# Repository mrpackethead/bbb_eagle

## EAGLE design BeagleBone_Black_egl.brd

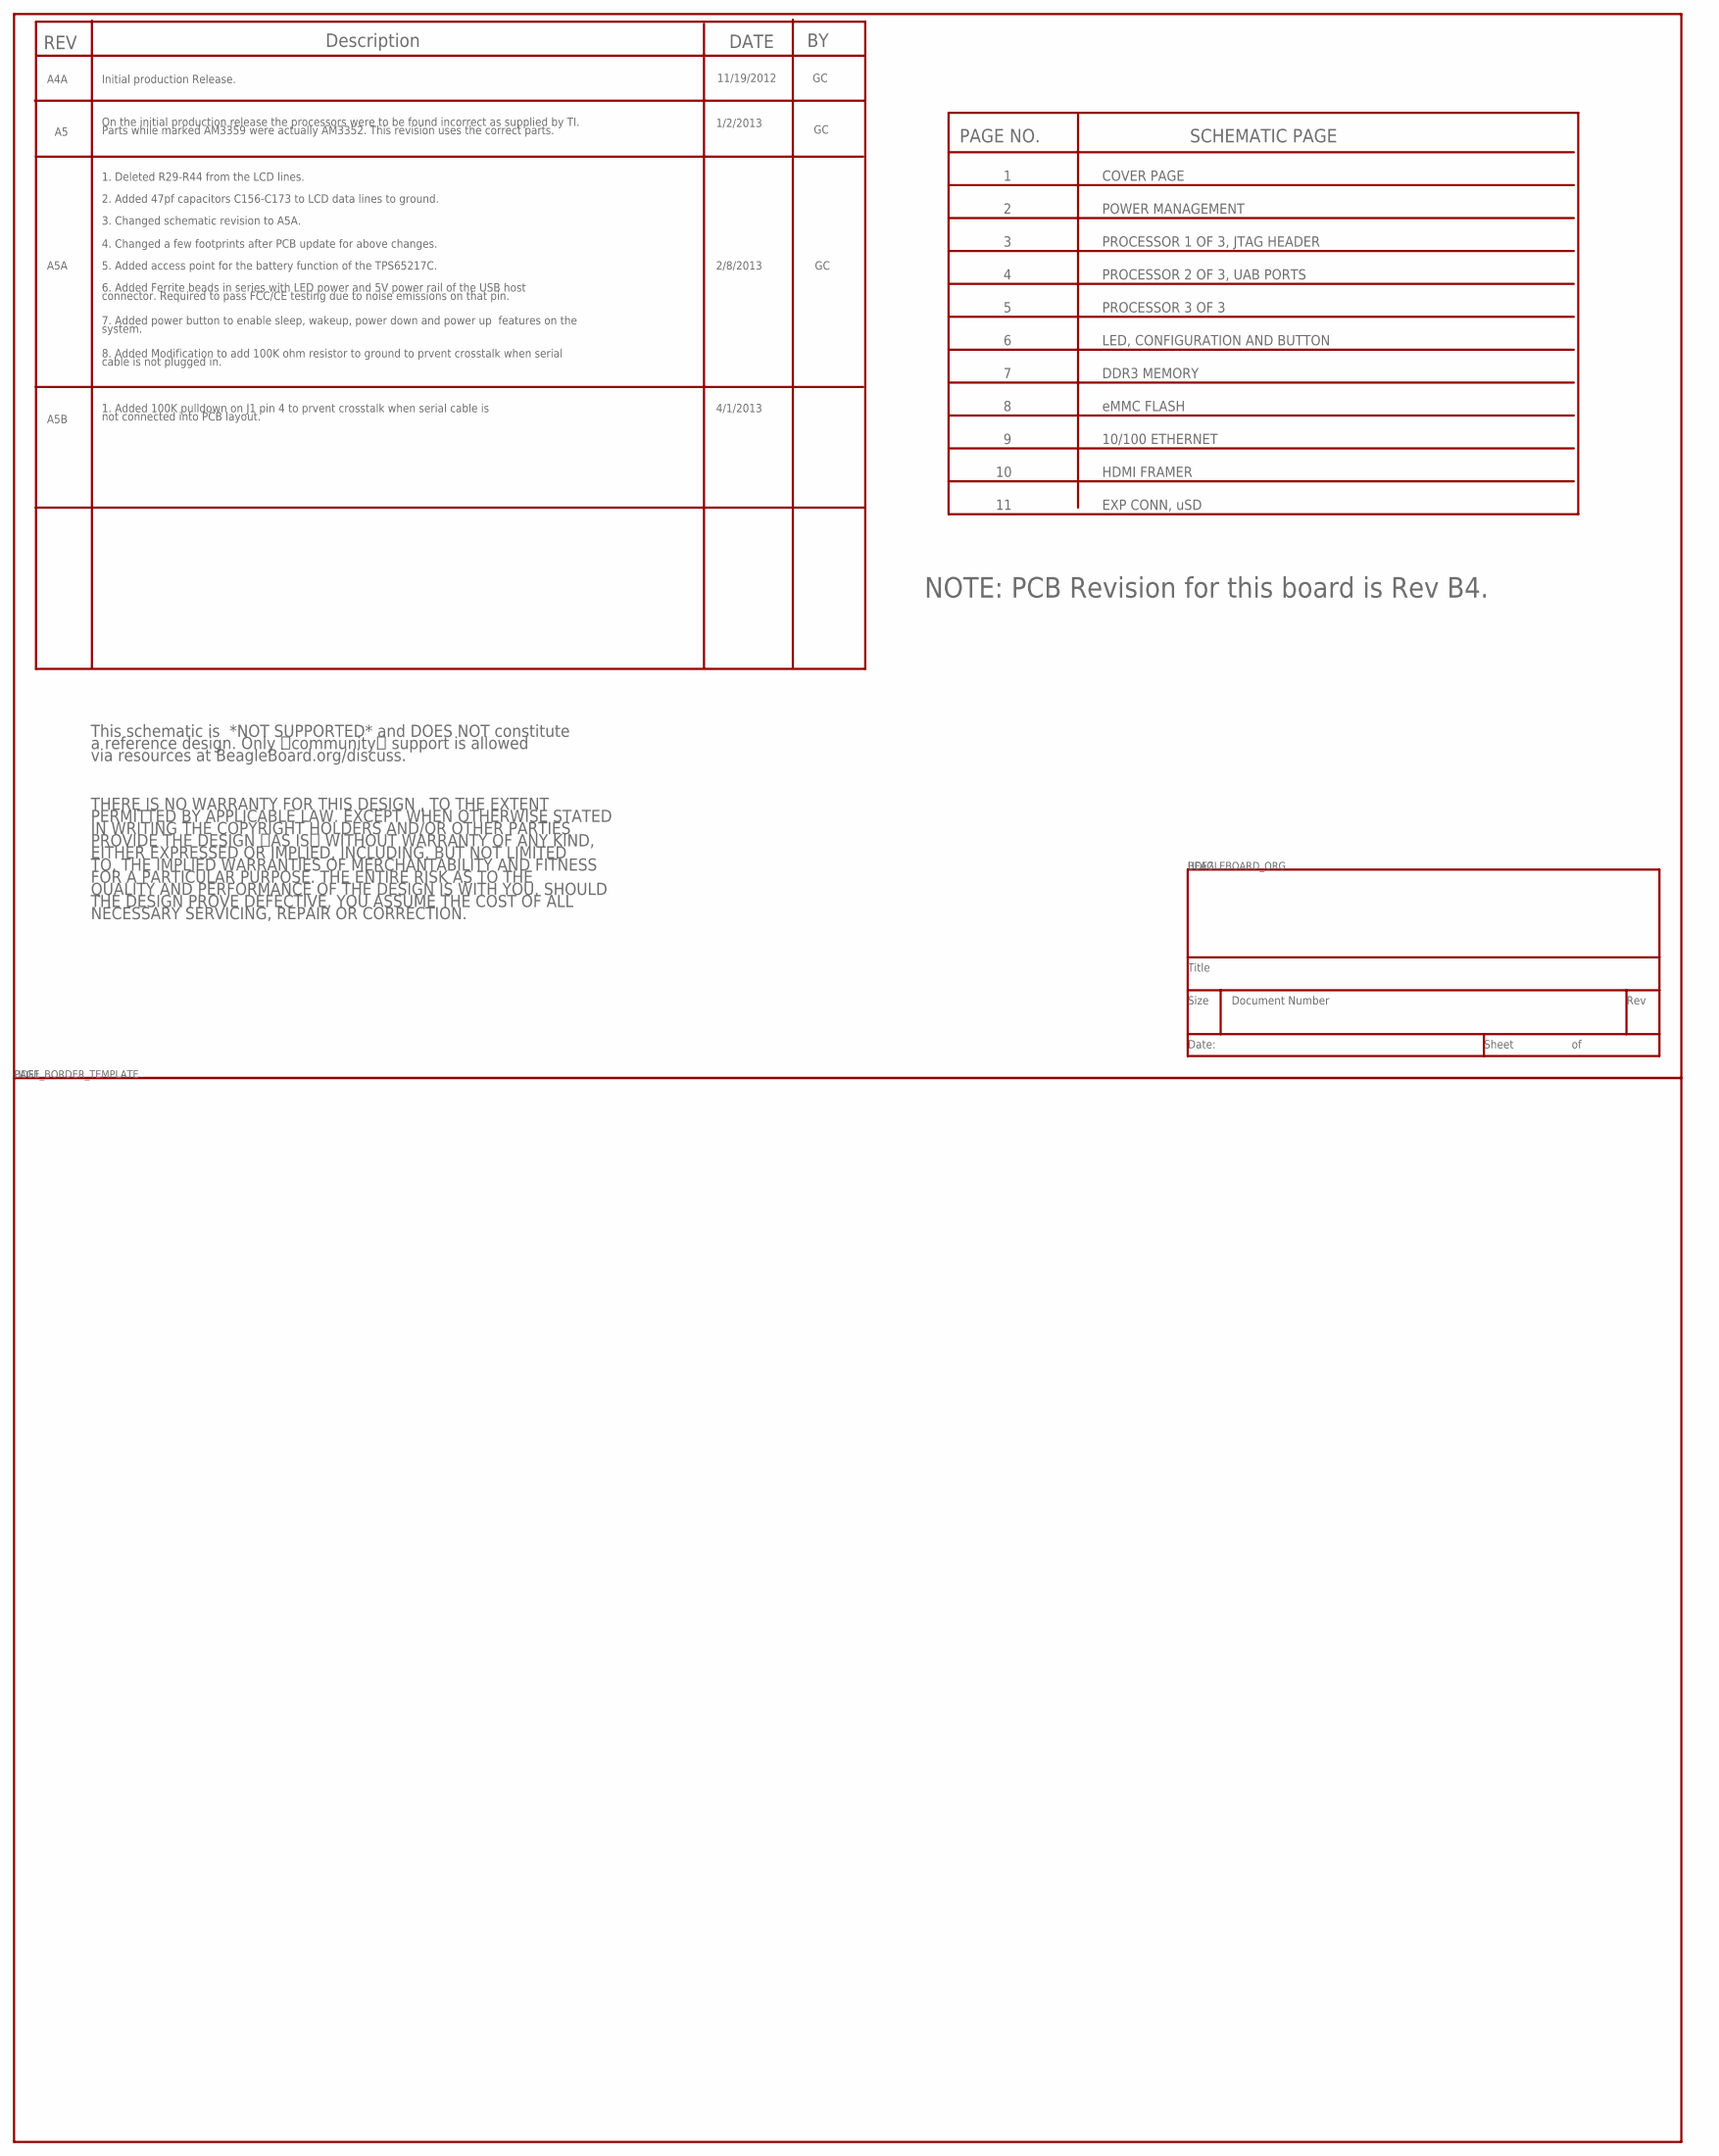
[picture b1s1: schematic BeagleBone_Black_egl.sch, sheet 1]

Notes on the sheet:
eMMC FLASH
HDMI FRAMER
10/100 ETHERNET
DDR3 MEMORY
PROCESSOR 2 OF 3, UAB PORTS
LED, CONFIGURATION AND BUTTON
SCHEMATIC PAGE
PAGE NO.
PROCESSOR 3 OF 3
PROCESSOR 1 OF 3, JTAG HEADER
POWER MANAGEMENT
COVER PAGE
This schematic is *NOT SUPPORTED* and DOES NOT constitute
a reference design. Only community support is allowed
via resources at BeagleBoard.org/discuss.
THERE IS NO WARRANTY FOR THIS DESIGN , TO THE EXTENT
PERMITTED BY APPLICABLE LAW. EXCEPT WHEN OTHERWISE STATED
IN WRITING THE COPYRIGHT HOLDERS AND/OR OTHER PARTIES
PROVIDE THE DESIGN AS IS WITHOUT WARRANTY OF ANY KIND,
EITHER EXPRESSED OR IMPLIED, INCLUDING, BUT NOT LIMITED
TO, THE IMPLIED WARRANTIES OF MERCHANTABILITY AND FITNESS
FOR A PARTICULAR PURPOSE. THE ENTIRE RISK AS TO THE
QUALITY AND PERFORMANCE OF THE DESIGN IS WITH YOU. SHOULD
THE DESIGN PROVE DEFECTIVE, YOU ASSUME THE COST OF ALL
NECESSARY SERVICING, REPAIR OR CORRECTION.
EXP CONN, uSD
NOTE: PCB Revision for this board is Rev B4.
REV
Description
DATE
11/19/2012
Initial production Release.
A4A
On the initial production release the processors were to be found incorrect as supplied by TI.
Parts while marked AM3359 were actually AM3352. This revision uses the correct parts.
1/2/2013
1. Deleted R29-R44 from the LCD lines.
2. Added 47pf capacitors C156-C173 to LCD data lines to ground.
3. Changed schematic revision to A5A.
A5A

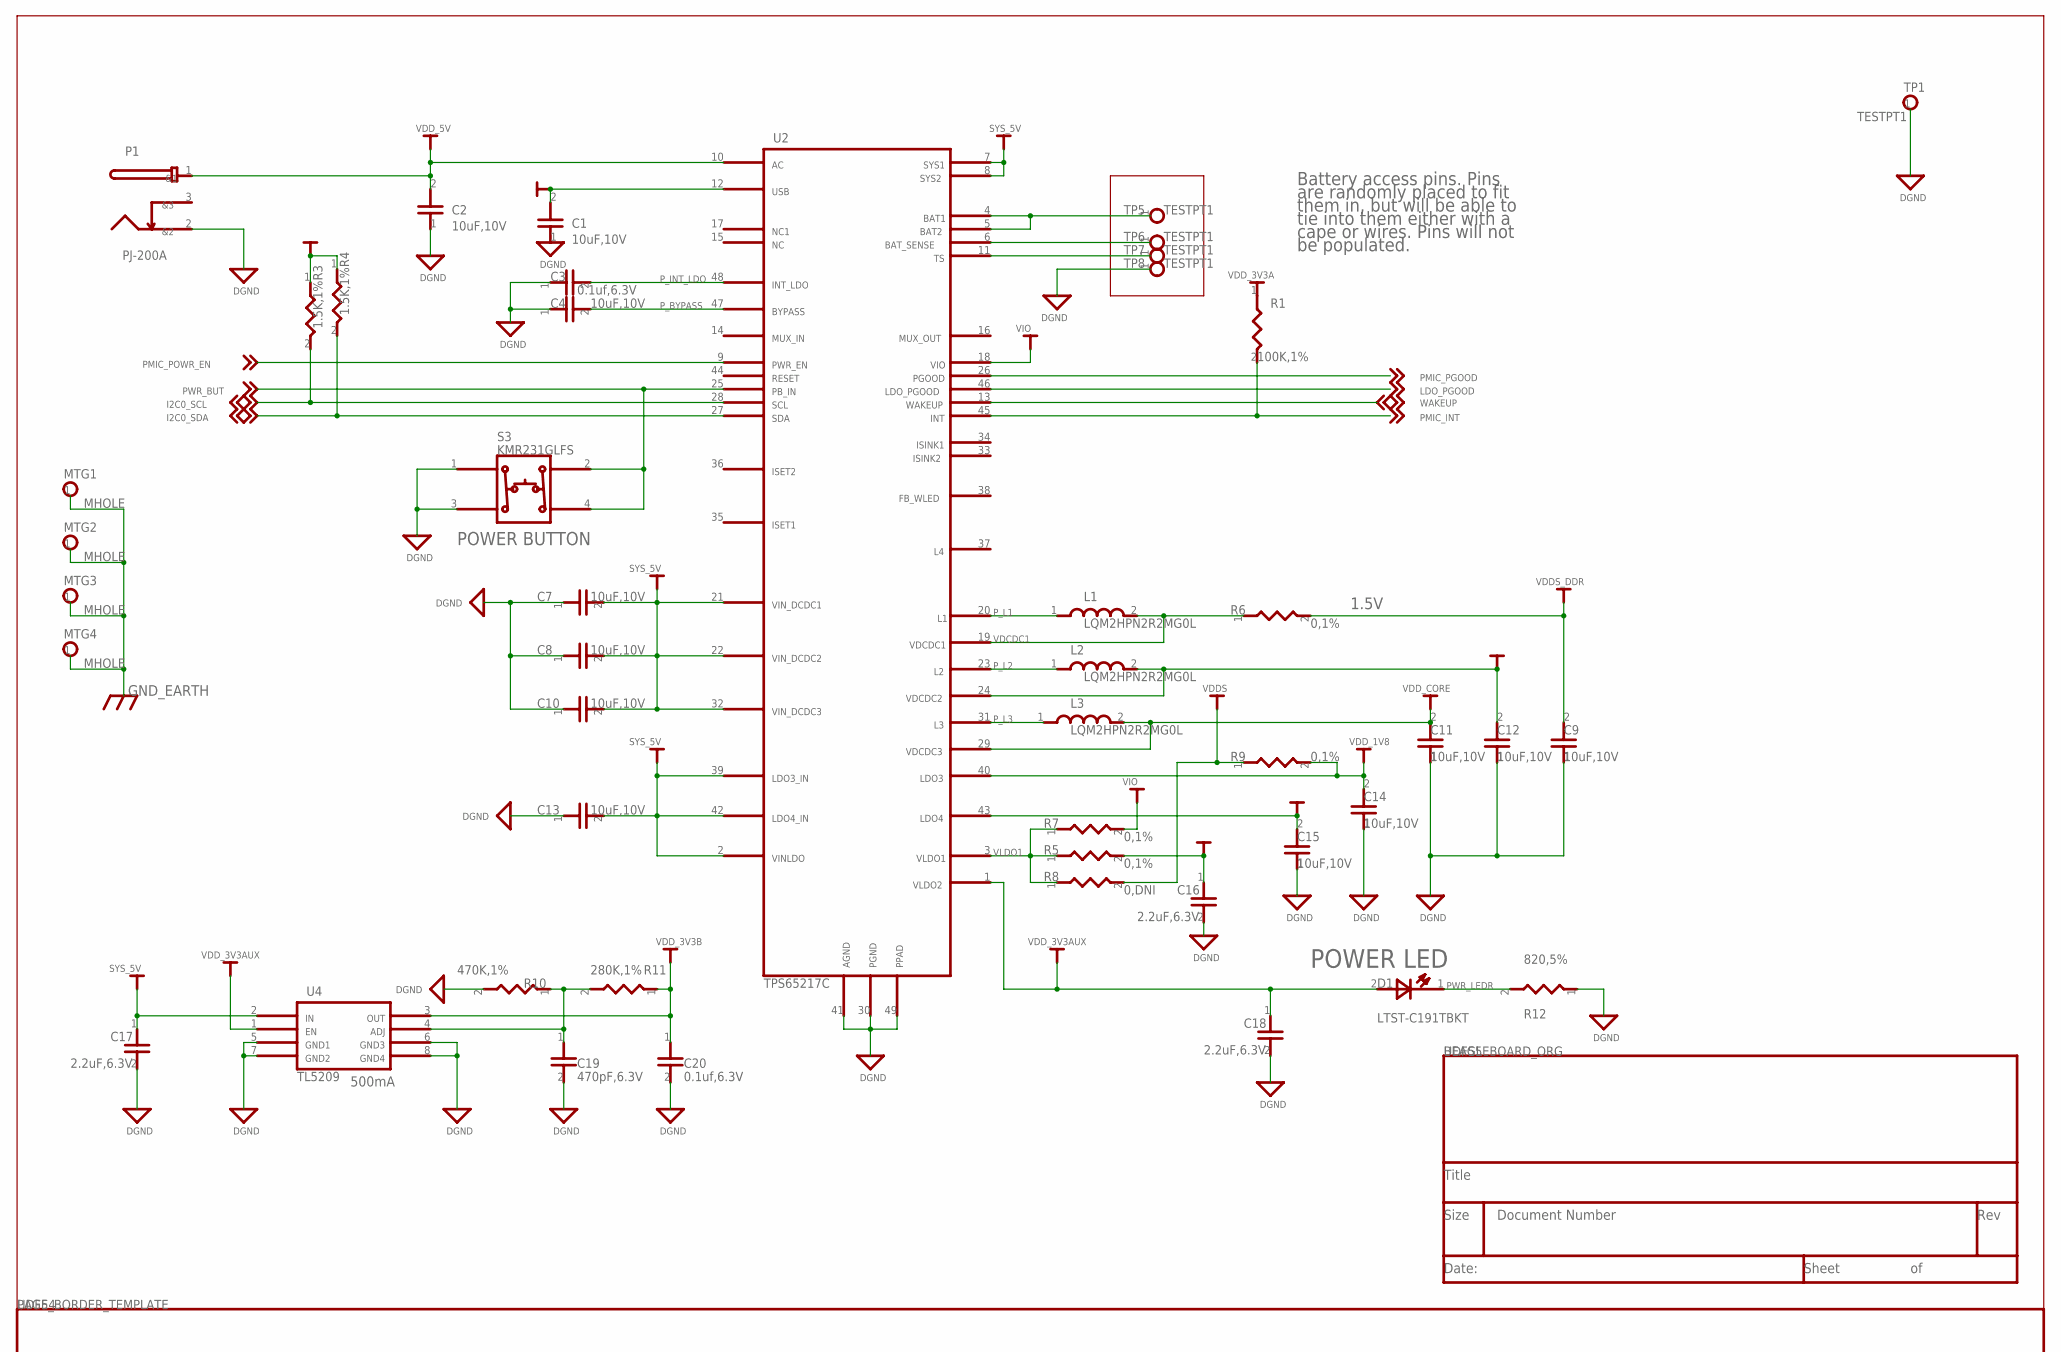
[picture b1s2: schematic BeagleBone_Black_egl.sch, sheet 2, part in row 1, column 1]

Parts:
C1, C2, C4, C7, C8, C9, C10, C11, C12, C13, C14, C15: 10uF,10V; 805
C3, C20: 0.1uf,6.3V; 402
C16, C17, C18: 2.2uF,6.3V; 402
C19: 470pF,6.3V; 402
D1: LTST-C191TBKT; LED_0603
L1, L2, L3: LQM2HPN2R2MG0L; 2520
MTG1, MTG2, MTG3, MTG4: MHOLE; MTGH200C125D_PL
P1: PJ-200A; CONN3-PWR-PJ102A
R1: 100K,1%; 402
R3, R4: 1.5K,1%; 402
R5, R6, R7, R9: 0,1%; 402
R8: 0,DNI; 402
R10: 470K,1%; 402
R11: 280K,1%; 402
R12: 820,5%; 402
S3: KMR231GLFS; SW4SMD_63X161LS
TP1: TESTPT1; TP1-8040
TP5, TP6, TP7, TP8: TESTPT1; TP60C33D
U2: TPS65217C; U_48_RSL
U4: TL5209; SO8-25X75

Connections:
DGND: C1.1, C2.1, C3.1, C4.1, C7.1, C8.1, C9.1, C10.1, C11.1, C12.1, C13.1, C14.1, C15.1, C16.2, C17.2, C18.2, C19.2, C20.2, P1.2 (3), R10.2, R12.1, S3.1, S3.3, TP1.1, TP8.1, U2.30 (46), U2.41 (45), U2.49, U4.5 (3), U4.6, U4.7, U4.8; also elsewhere on the board
GND_EARTH: MTG1.1, MTG2.1, MTG3.1, MTG4.1; also elsewhere on the board
I2C0_SCL: R3.2, U2.28 (16); also elsewhere on the board
I2C0_SDA: R4.2, U2.27 (17); also elsewhere on the board
LDO_PGOOD: U2.46 (26); also elsewhere on the board
N21757673: C19.1, R10.1, R11.2, U4.4 (5)
N22420400: TP5.1, U2.4 (5), U2.5 (6)
N22420444: TP6.1, U2.6 (7)
N22420447: TP7.1, U2.11 (8)
PMIC_INT: R1.2, U2.45 (28); also elsewhere on the board
PMIC_PGOOD: U2.26 (25); also elsewhere on the board
PMIC_POWR_EN: U2.9 (13); also elsewhere on the board
PWR_BUT: S3.2, S3.4, U2.25 (15); also elsewhere on the board
PWR_LEDR: D1.1, R12.2
P_BYPASS: C4.2, U2.47 (12)
P_INT_LDO: C3.2, U2.48 (11)
P_L1: L1.1, U2.20 (30)
P_L2: L2.1, U2.23 (33)
P_L3: L3.1, U2.31 (36)
SYS_5V: C7.2, C8.2, C10.2, C13.2, C17.1, U2.2 (42), U2.7 (3), U2.8 (4), U2.21 (29), U2.22 (32), U2.32 (35), U2.39 (40), U2.42 (41), U4.2 (1); also elsewhere on the board
USB_DC: C1.2, U2.12 (2); also elsewhere on the board
VDCDC1: L1.2, R6.1, U2.19 (31)
VDDS: R8.2, R9.1; also elsewhere on the board
VDDS_DDR: C9.2, R6.2; also elsewhere on the board
VDD_1V8: C14.2, R9.2, U2.40 (38); also elsewhere on the board
VDD_3V3A: C15.2, R1.1, R3.1, R4.1, U2.43 (39); also elsewhere on the board
VDD_3V3AUX: C18.1, D1.2, U2.1 (44), U4.1 (4)
VDD_3V3B: C20.1, R11.1, U4.3 (2); also elsewhere on the board
VDD_5V: C2.2, P1.1, U2.10 (1); also elsewhere on the board
VDD_CORE: C11.2, L3.2, U2.29 (37); also elsewhere on the board
VDD_MPU: C12.2, L2.2, U2.24 (34); also elsewhere on the board
VIO: R7.2, U2.18 (24)
VLDO1: R5.1, R7.1, R8.1, U2.3 (43)
VRTC: C16.1, R5.2; also elsewhere on the board
WAKEUP: U2.13 (27); also elsewhere on the board

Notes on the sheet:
POWER LED
1.5V
500mA
Battery access pins. Pins
are randomly placed to fit
them in, but will be able to
tie into them either with a
cape or wires. Pins will not
be populated.
POWER BUTTON
DGND
GND_EARTH
I2C0_SCL
I2C0_SDA
LDO_PGOOD
PMIC_INT
PMIC_PGOOD
PMIC_POWR_EN
PWR_BUT
PWR_LEDR
P_BYPASS
P_INT_LDO
P_L1
P_L2
P_L3
SYS_5V
VDCDC1
VDDS
VDDS_DDR
VDD_1V8
VDD_3V3A
VDD_3V3AUX
VDD_3V3B
VDD_5V
VDD_CORE
VIO
VLDO1
WAKEUP

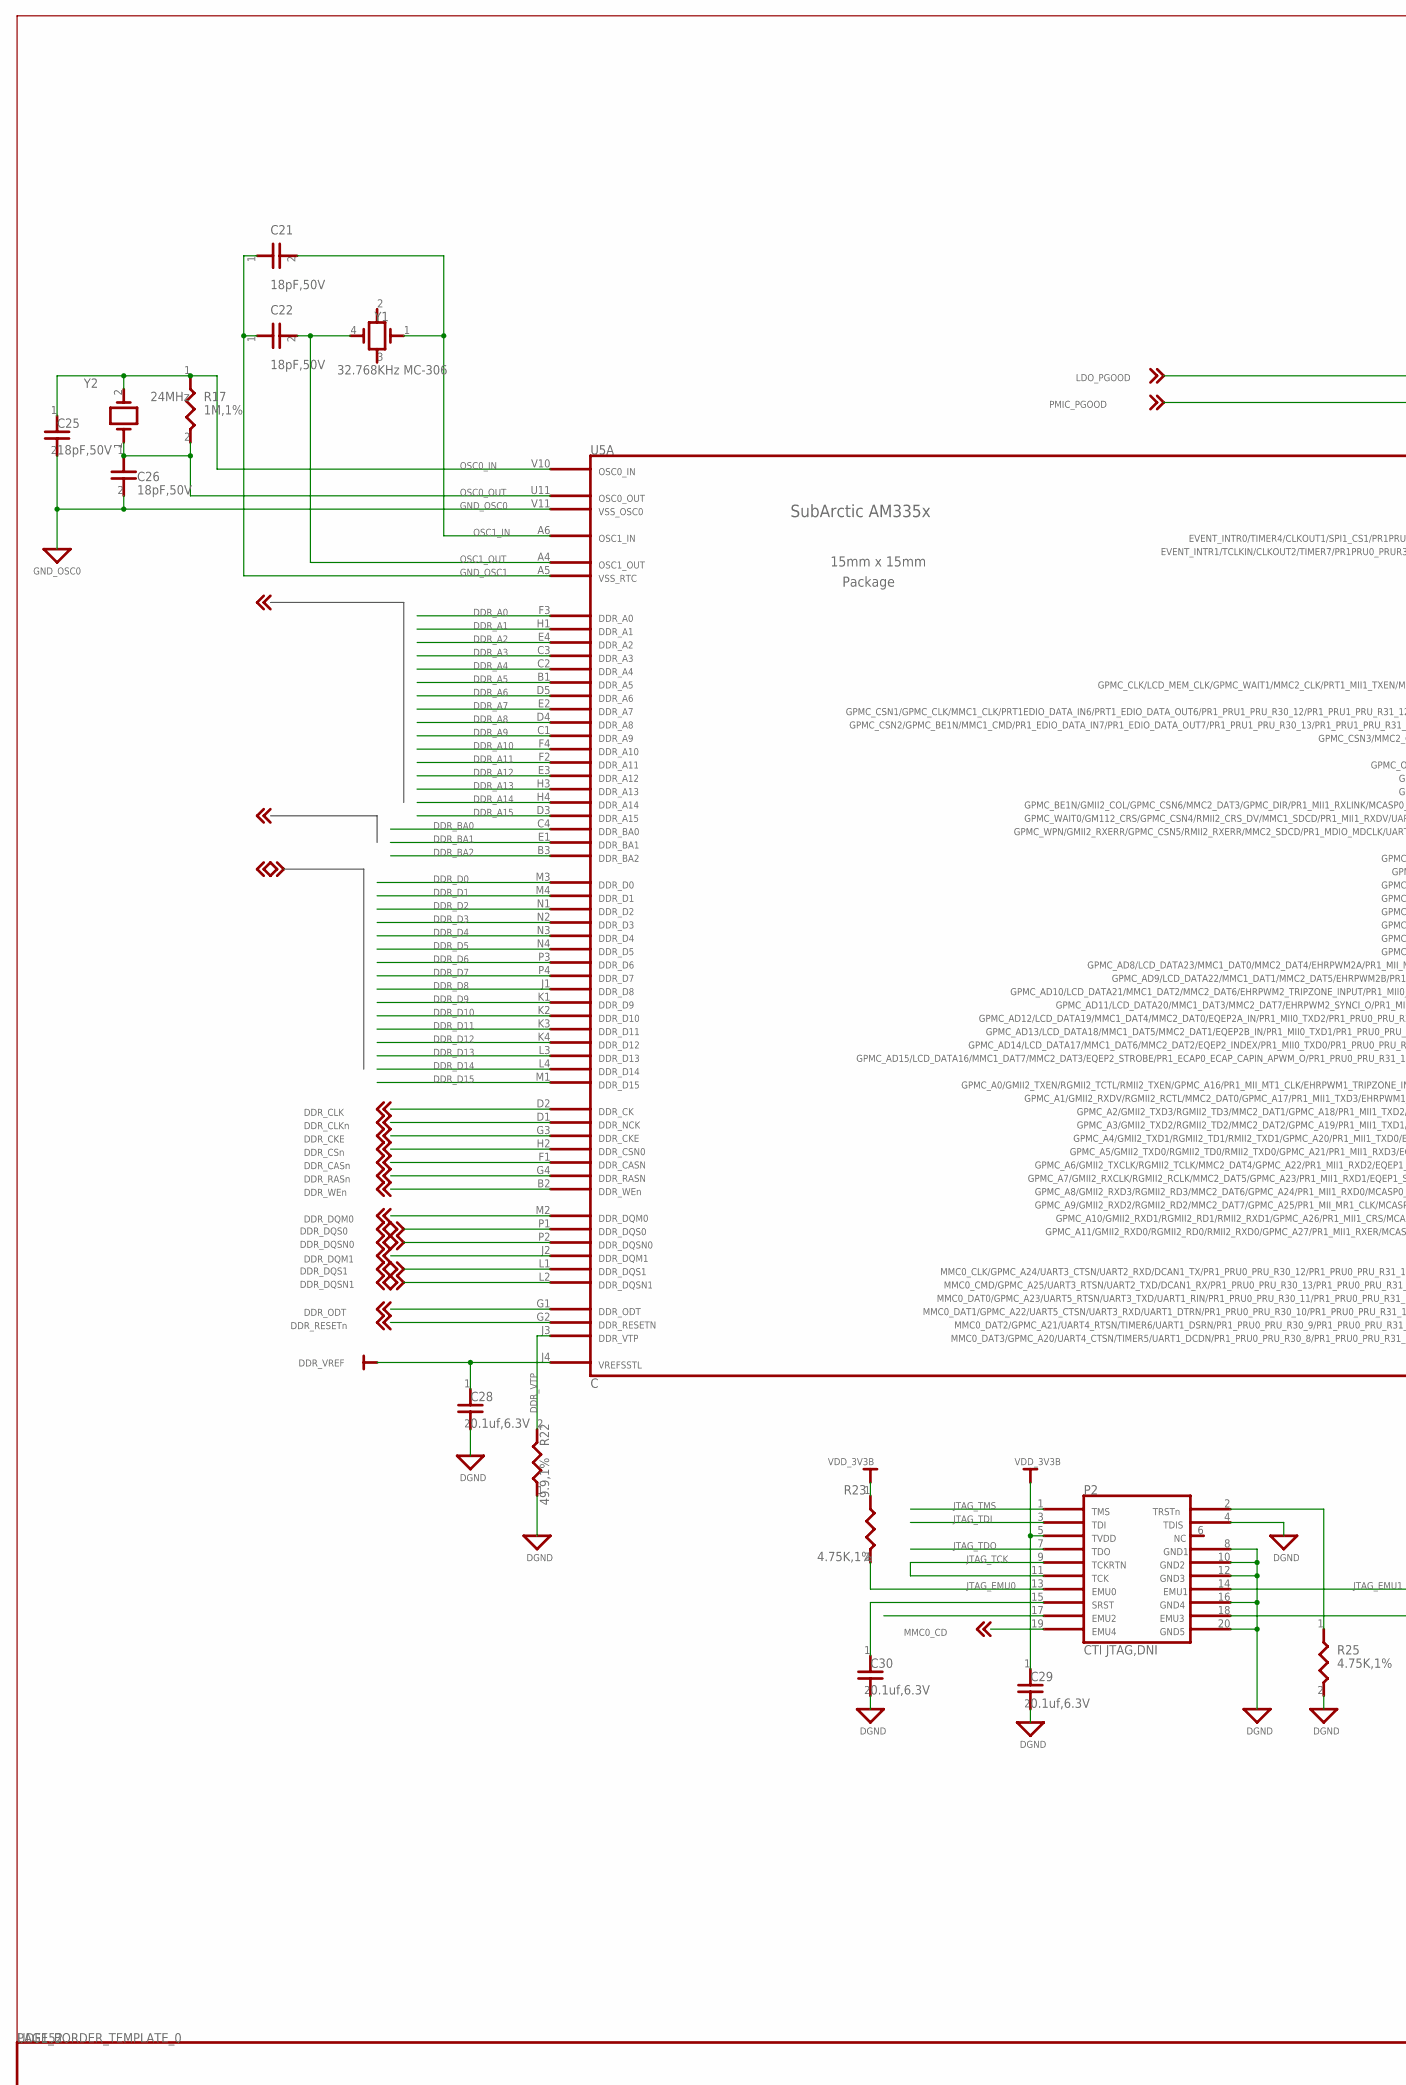
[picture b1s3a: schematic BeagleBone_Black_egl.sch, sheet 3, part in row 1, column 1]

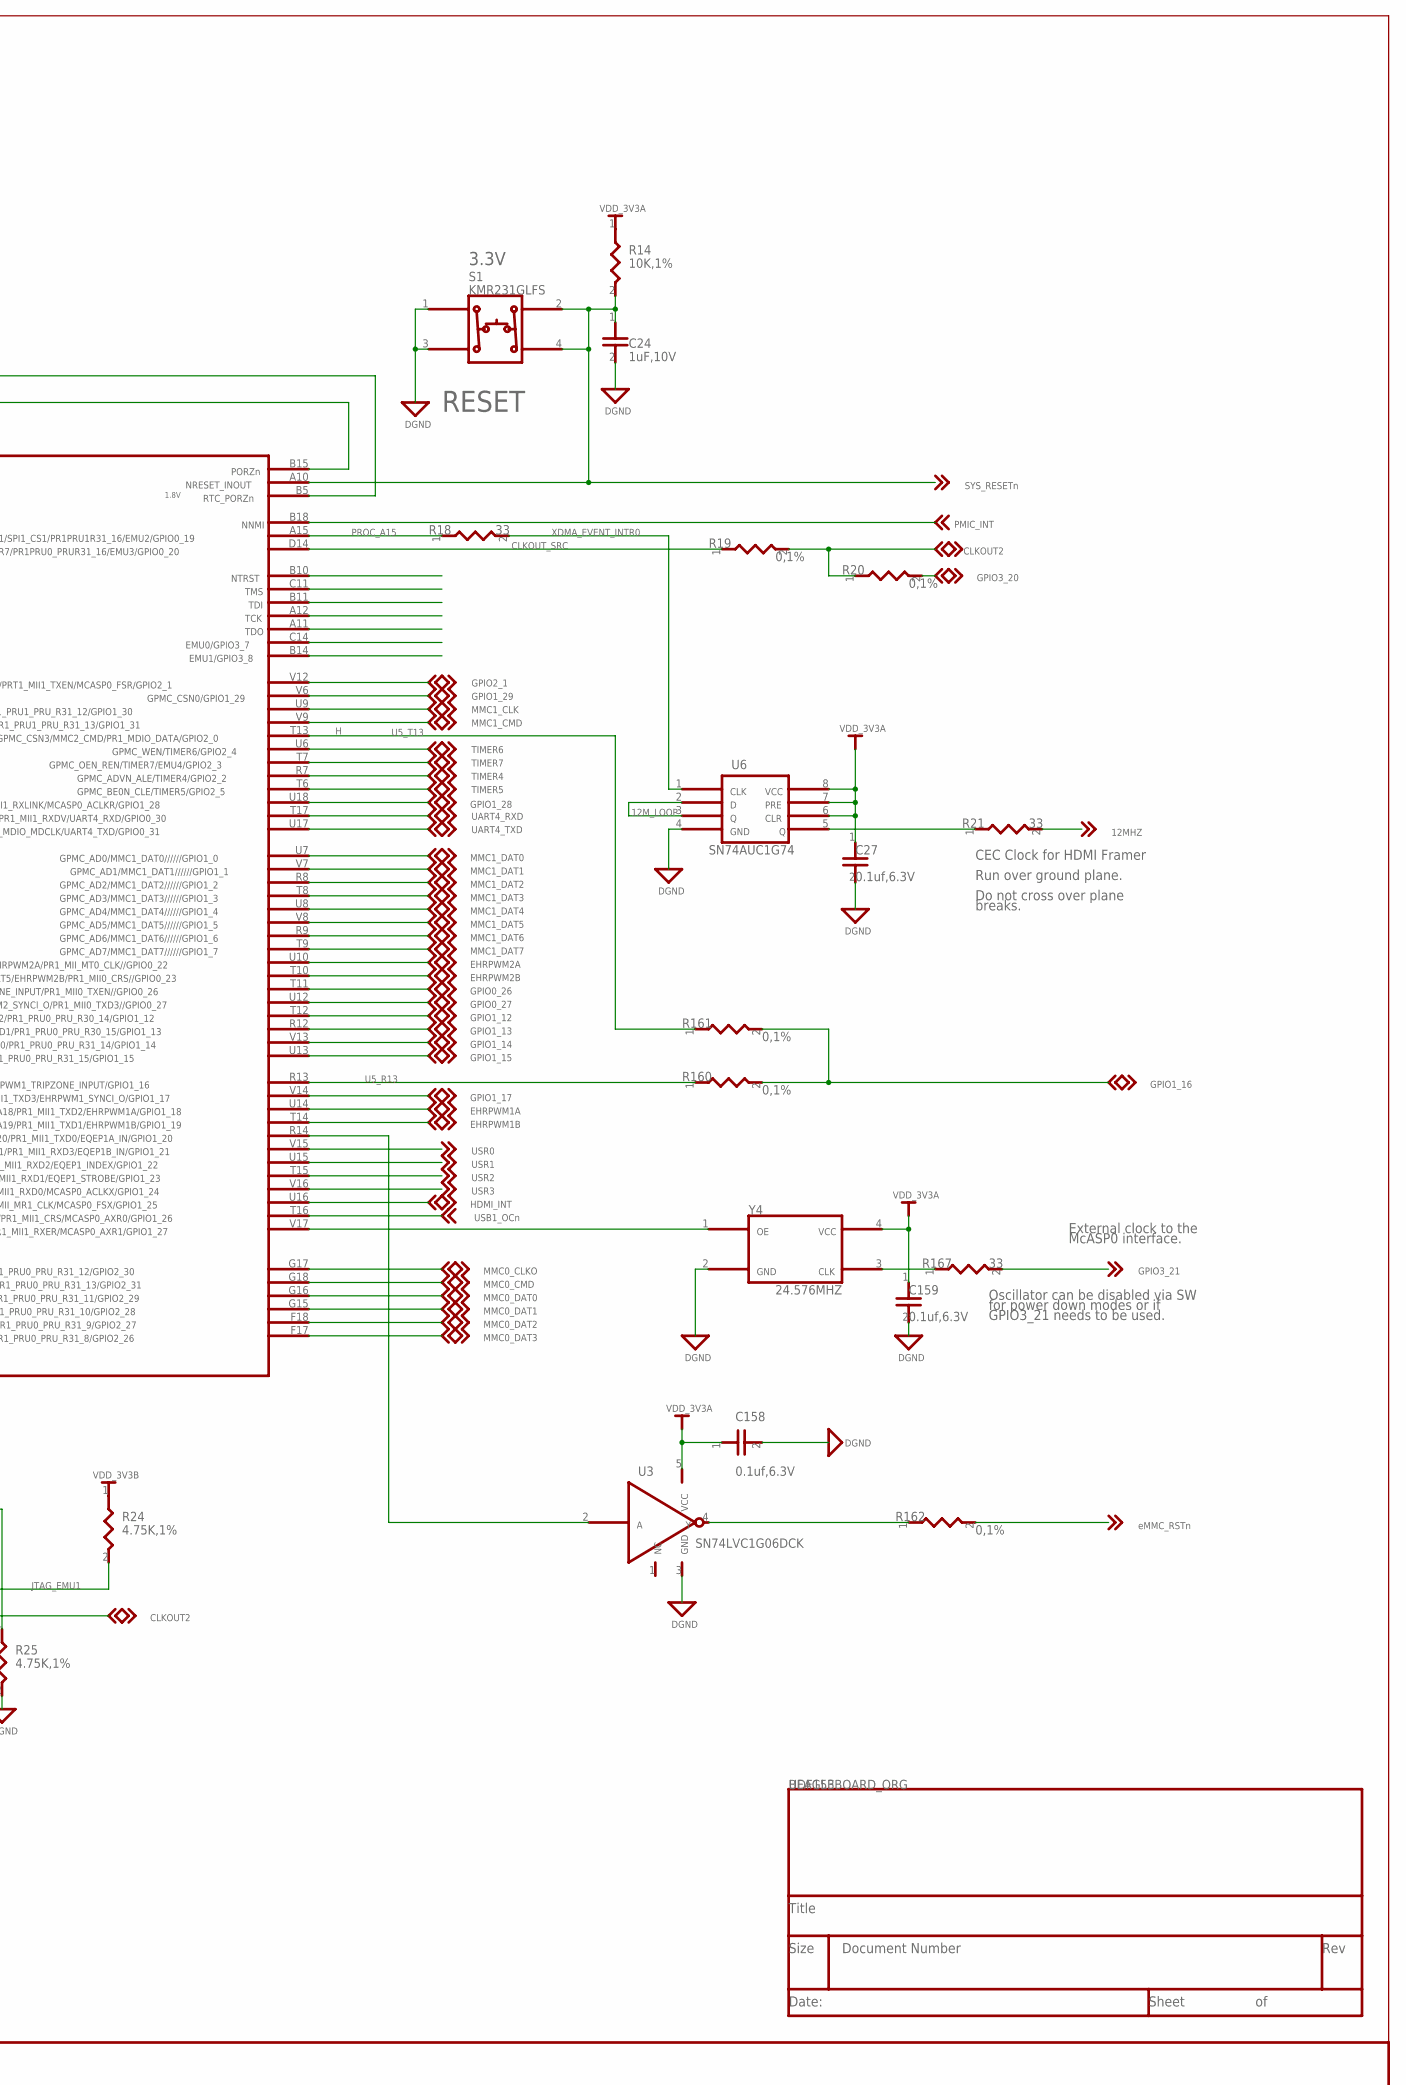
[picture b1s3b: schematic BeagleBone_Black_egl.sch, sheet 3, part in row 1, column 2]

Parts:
C21, C22, C25, C26: 18pF,50V; 402
C24: 1uF,10V; 402
C27, C28, C29, C30, C158, C159: 0.1uf,6.3V; 402
P2: CTI JTAG,DNI; HEADER10X2_SMD
R14: 10K,1%; 402
R17: 1M,1%; 402
R18, R21, R167: 33; 0402
R19, R20, R160, R161, R162: 0,1%; 402
R22: 49.9,1%; 402
R23, R24, R25: 4.75K,1%; 402
S1: KMR231GLFS; SW4SMD_63X161LS
U3: SN74LVC1G06DCK; DCK5_2P15X1P4
U5: C; AM33XX_15X15
U6: SN74AUC1G74; SOP8_DCT
Y1: 32.768KHz MC-306; XTAL4_126-216SMD
Y2: 24MHz; XTAL150SMD_125X196
Y4: 24.576MHZ; OSC4_61X65LS_79X98SMD

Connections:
12MHZ: R21.2; also elsewhere on the board
12M_LOOP: U6.2, U6.3
CLKOUT2: P2.18 (19), R19.2, R20.1; also elsewhere on the board
CLKOUT_SRC: R19.1, U5.D14 (54)
DDR_A0: U5.F3 (61); also elsewhere on the board
DDR_A1: U5.H1 (62); also elsewhere on the board
DDR_A2: U5.E4 (63); also elsewhere on the board
DDR_A3: U5.C3 (64); also elsewhere on the board
DDR_A4: U5.C2 (65); also elsewhere on the board
DDR_A5: U5.B1 (66); also elsewhere on the board
DDR_A6: U5.D5 (67); also elsewhere on the board
DDR_A7: U5.E2 (68); also elsewhere on the board
DDR_A8: U5.D4 (69); also elsewhere on the board
DDR_A9: U5.C1 (70); also elsewhere on the board
DDR_A10: U5.F4 (71); also elsewhere on the board
DDR_A11: U5.F2 (72); also elsewhere on the board
DDR_A12: U5.E3 (73); also elsewhere on the board
DDR_A13: U5.H3 (74); also elsewhere on the board
DDR_A14: U5.H4 (75); also elsewhere on the board
DDR_A15: U5.D3 (115); also elsewhere on the board
DDR_BA0: U5.C4 (98); also elsewhere on the board
DDR_BA1: U5.E1 (99); also elsewhere on the board
DDR_BA2: U5.B3 (100); also elsewhere on the board
DDR_CASN: U5.F1 (95); also elsewhere on the board
DDR_CKE: U5.G3 (112); also elsewhere on the board
DDR_CLK: U5.D2 (92); also elsewhere on the board
DDR_CLKN: U5.D1 (93); also elsewhere on the board
DDR_CSN: U5.H2 (94); also elsewhere on the board
DDR_D0: U5.M3 (76); also elsewhere on the board
DDR_D1: U5.M4 (77); also elsewhere on the board
DDR_D2: U5.N1 (78); also elsewhere on the board
DDR_D3: U5.N2 (79); also elsewhere on the board
DDR_D4: U5.N3 (80); also elsewhere on the board
DDR_D5: U5.N4 (81); also elsewhere on the board
DDR_D6: U5.P3 (82); also elsewhere on the board
DDR_D7: U5.P4 (83); also elsewhere on the board
DDR_D8: U5.J1 (84); also elsewhere on the board
DDR_D9: U5.K1 (85); also elsewhere on the board
DDR_D10: U5.K2 (86); also elsewhere on the board
DDR_D11: U5.K3 (87); also elsewhere on the board
DDR_D12: U5.K4 (88); also elsewhere on the board
DDR_D13: U5.L3 (89); also elsewhere on the board
DDR_D14: U5.L4 (90); also elsewhere on the board
DDR_D15: U5.M1 (91); also elsewhere on the board
DDR_DQM0: U5.M2 (101); also elsewhere on the board
DDR_DQM1: U5.J2 (104); also elsewhere on the board
DDR_DQS0: U5.P1 (102); also elsewhere on the board
DDR_DQS1: U5.L1 (105); also elsewhere on the board
DDR_DQSN0: U5.P2 (103); also elsewhere on the board
DDR_DQSN1: U5.L2 (106); also elsewhere on the board
DDR_ODT: U5.G1 (107); also elsewhere on the board
DDR_RASN: U5.G4 (96); also elsewhere on the board
DDR_RESETN: U5.G2 (113); also elsewhere on the board
DDR_VREF: C28.1, U5.J4 (117); also elsewhere on the board
DDR_VTP: R22.2, U5.J3 (114)
DDR_WEN: U5.B2 (97); also elsewhere on the board
DGND: C24.2, C27.2, C28.2, C29.2, C30.2, C158.2, C159.2, P2.4 (12), P2.8 (14), P2.10 (15), P2.12 (16), P2.16 (18), P2.20, R22.1, R25.2, S1.1, S1.3, U3.3, U6.4, Y4.2; also elsewhere on the board
EHRPWM1A: U5.U14 (34); also elsewhere on the board
EHRPWM1B: U5.T14 (35); also elsewhere on the board
EHRPWM2A: U5.U10 (24); also elsewhere on the board
EHRPWM2B: U5.T10 (25); also elsewhere on the board
EMMC_RSTN: R162.2; also elsewhere on the board
GND_OSC0: C25.2, C26.2, U5.V11 (110)
GND_OSC1: C21.1, C22.1, U5.A5 (109)
GPIO0_26: U5.T11 (26); also elsewhere on the board
GPIO0_27: U5.U12 (27); also elsewhere on the board
GPIO1_12: U5.T12 (28); also elsewhere on the board
GPIO1_13: U5.R12 (29); also elsewhere on the board
GPIO1_14: U5.V13 (30); also elsewhere on the board
GPIO1_15: U5.U13 (31); also elsewhere on the board
GPIO1_16: R160.2, R161.2; also elsewhere on the board
GPIO1_17: U5.V14 (33); also elsewhere on the board
GPIO1_28: U5.U18 (14); also elsewhere on the board
GPIO1_29: U5.V6 (6); also elsewhere on the board
GPIO2_1: U5.V12 (5); also elsewhere on the board
GPIO3_20: R20.2; also elsewhere on the board
GPIO3_21: R167.2; also elsewhere on the board
HDMICLK_DISN: U5.V17 (43), Y4.1
HDMI_INT: U5.U16 (41); also elsewhere on the board
JTAG_EMU0: P2.13 (7), R23.2, U5.C14 (60)
JTAG_EMU1: P2.14 (17), R24.2, U5.B14 (108)
JTAG_TCK: P2.9 (5), P2.11 (6), U5.A12 (57)
JTAG_TDI: P2.3 (2), U5.B11 (58)
JTAG_TDO: P2.7 (4), U5.A11 (59)
JTAG_TMS: P2.1, U5.C11 (55)
JTAG_TRSTN: P2.2 (11), R25.1, U5.B10 (56)
LDO_PGOOD: U5.B5 (116); also elsewhere on the board
MMC0_CD: P2.19 (10); also elsewhere on the board
MMC0_CLKO: U5.G17 (44); also elsewhere on the board
MMC0_CMD: U5.G18 (45); also elsewhere on the board
MMC0_DAT0: U5.G16 (46); also elsewhere on the board
MMC0_DAT1: U5.G15 (47); also elsewhere on the board
MMC0_DAT2: U5.F18 (48); also elsewhere on the board
MMC0_DAT3: U5.F17 (49); also elsewhere on the board
MMC1_CLK: U5.U9 (7); also elsewhere on the board
MMC1_CMD: U5.V9 (8); also elsewhere on the board
MMC1_DAT0: U5.U7 (16); also elsewhere on the board
MMC1_DAT1: U5.V7 (17); also elsewhere on the board
MMC1_DAT2: U5.R8 (18); also elsewhere on the board
MMC1_DAT3: U5.T8 (19); also elsewhere on the board
MMC1_DAT4: U5.U8 (20); also elsewhere on the board
MMC1_DAT5: U5.V8 (21); also elsewhere on the board
MMC1_DAT6: U5.R9 (22); also elsewhere on the board
MMC1_DAT7: U5.T9 (23); also elsewhere on the board
N22248684: R167.1, Y4.3 (4)
N22248838: R21.1, U6.5
N22287501: R162.1, U3.4 (2)
N22287555: U3.2 (1), U5.R14 (36)
OSC0_IN: C25.1, R17.1, U5.V10 (3), Y2.2
OSC0_OUT: C26.1, R17.2, U5.U11 (4), Y2.1
OSC1_IN: C21.2, U5.A6 (1), Y1.1
OSC1_OUT: C22.2, U5.A4 (2), Y1.4 (2)
PMIC_INT: U5.B18 (52); also elsewhere on the board
PMIC_PGOOD: U5.B15 (50); also elsewhere on the board
PROC_A15: R18.1, U5.A15 (53)
SYS_RESETN: C24.1, C30.1, P2.15 (8), R14.2, S1.2, S1.4, U5.A10 (51); also elsewhere on the board
TIMER4: U5.R7 (12); also elsewhere on the board
TIMER5: U5.T6 (13); also elsewhere on the board
TIMER6: U5.U6 (9); also elsewhere on the board
TIMER7: U5.T7 (10); also elsewhere on the board
U5_R13: R160.1, U5.R13 (32)
U5_T13: R161.1, U5.T13 (11)
UART4_RXD: U5.T17 (15); also elsewhere on the board
UART4_TXD: U5.U17 (111); also elsewhere on the board
USB1_OCN: U5.T16 (42); also elsewhere on the board
USR0: U5.V15 (37); also elsewhere on the board
USR1: U5.U15 (38); also elsewhere on the board
USR2: U5.T15 (39); also elsewhere on the board
USR3: U5.V16 (40); also elsewhere on the board
VDD_3V3A: C27.1, C158.1, C159.1, R14.1, U3.5 (4), U6.6, U6.7, U6.8, Y4.4 (3); also elsewhere on the board
VDD_3V3B: C29.1, P2.5 (3), R23.1, R24.1; also elsewhere on the board
XDMA_EVENT_INTR0: P2.17 (9), R18.2, U6.1

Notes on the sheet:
RESET
CEC Clock for HDMI Framer
Run over ground plane.
Do not cross over plane
breaks.
3.3V
External clock to the
McASP0 interface.
Oscillator can be disabled via SW
for power down modes or if
GPIO3_21 needs to be used.
DGND
LDO_PGOOD
PMIC_INT
PMIC_PGOOD
VDD_3V3A
VDD_3V3B
12MHZ
12M_LOOP
CLKOUT2
CLKOUT_SRC
DDR_A0
DDR_A1
DDR_A10
DDR_A11
DDR_A12
DDR_A13
DDR_A14
DDR_A15
DDR_A2
DDR_A3
DDR_A4
DDR_A5
DDR_A6
DDR_A7
DDR_A8
DDR_A9
DDR_BA0
DDR_BA1
DDR_BA2

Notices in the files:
BeagleBone_Black_egl.brd:
For more information, see http://creativecommons.org/license/results-one?license_code=by-sa
a letter to Creative Commons, 171 Second Street, Suite 300, San Francisco, California, 94105, USA.
To view a copy of this license, visit http://creativecommons.org/licenses/by-sa/3.0/ or send
This work is licensed under the Creative Commons Attribution-Share Alike 3.0 Unported License.
